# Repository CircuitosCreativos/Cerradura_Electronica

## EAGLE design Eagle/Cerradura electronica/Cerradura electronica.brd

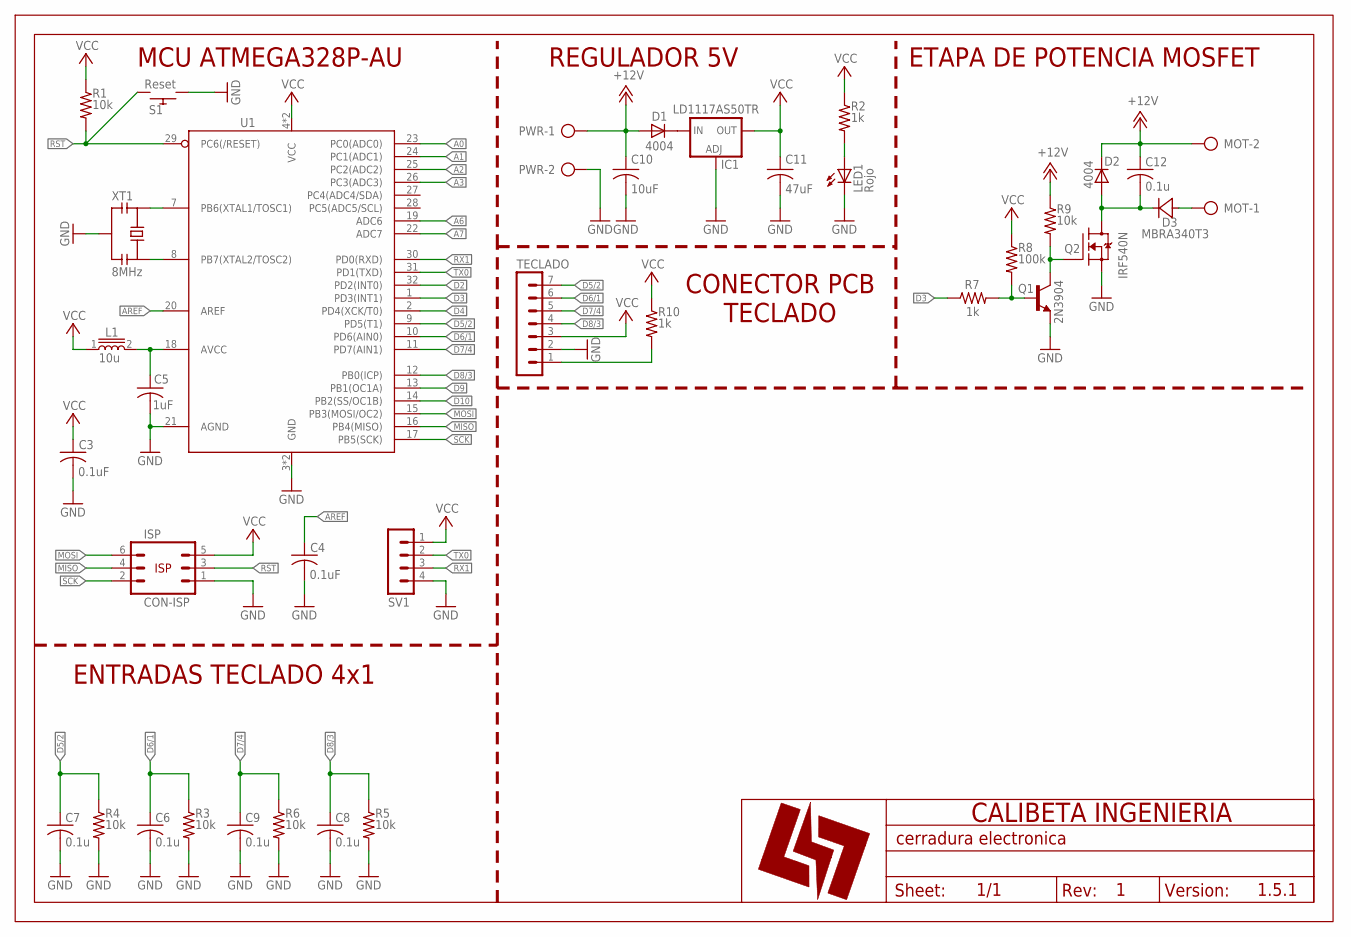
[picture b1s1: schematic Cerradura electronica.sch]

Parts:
C3, C4: 0.1uF; C0805
C5: 1uF; C0805
C6, C7, C8, C9, C12: 0.1u; C0805
C10: 10uF; C1206
C11: 47uF; C1206
D1, D2: 4004; DO-214AC
D3: MBRA340T3; SMA
IC1: LD1117AS50TR; SOT-223
ISP: CON-ISP; HEADER-M2X3
L1: 10u; L0805
LED1: Rojo; LED0805-ROJO
MOT: AK500-2
PWR: AK500-2
Q1: 2N3904; SOT-23_BEC
Q2: IRF540N; TO-263
R1, R3, R4, R5, R6, R9: 10k; R0805
R2, R7, R10: 1k; R0805
R8: 100k; R0805
S1: Reset; ST-SMD-6X3.5MM
SV1: MA04-1
TECLADO: MA07-1
U1: ATMEGA328P-AU; TQFP32
U$1: A4_H-LOGO; LOGO-10MM
XT1: 8MHz; 3-SMD

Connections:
+12V: C10.1, C12.1, D1.A, D2.K (C), MOT.2, PWR.1, R9.1
A0: U1.23 (PC0(ADC0))
A1: U1.24 (PC1(ADC1))
A2: U1.25 (PC2(ADC2))
A3: U1.26 (PC3(ADC3))
A6: U1.19 (ADC6)
A7: U1.22 (ADC7)
AREF: C4.1, U1.20 (AREF)
AVCC: C5.1, L1.2, U1.18 (AVCC)
D2: U1.32 (PD2(INT0))
D3: R7.1, U1.1 (PD3(INT1))
D4: U1.2 (PD4(XCK/T0))
D5/2: C7.1, R4.1, TECLADO.7, U1.9 (PD5(T1))
D6/1: C6.1, R3.1, TECLADO.6, U1.10 (PD6(AIN0))
D7/4: C9.1, R6.1, TECLADO.5, U1.11 (PD7(AIN1))
D8/3: C8.1, R5.1, TECLADO.4, U1.12 (PB0(ICP))
D9: U1.13 (PB1(OC1A))
D10: U1.14 (PB2(SS/OC1B))
GND: C3.2, C4.2, C5.2, C6.2, C7.2, C8.2, C9.2, C10.2, C11.2, IC1.1 (ADJ), ISP.1, LED1.C, PWR.2, Q1.E, Q2.3 (S), R3.2, R4.2, R5.2, R6.2, S1.1, SV1.4, TECLADO.2, U1.3 (GND), U1.5 (GND), U1.21 (AGND), XT1.2 (GND)
MISO: ISP.4, U1.16 (PB4(MISO))
MOSI: ISP.6, U1.15 (PB3(MOSI/OC2))
MOT: D3.A, MOT.1
unnamed: LED1.A, R2.2
unnamed: Q1.B, R7.2, R8.2
unnamed: D1.K (C), IC1.3 (IN)
unnamed: Q1.C, Q2.1 (G), R9.2
unnamed: U1.7 (PB6(XTAL1/TOSC1)), XT1.1 (X1)
unnamed: U1.8 (PB7(XTAL2/TOSC2)), XT1.3 (X2)
unnamed: R10.2, TECLADO.1
ON: C12.2, D2.A, D3.C, Q2.2 (D)
RST: ISP.3, R1.2, S1.2, U1.29 (PC6(/RESET))
RX1: SV1.3, U1.30 (PD0(RXD))
SCK: ISP.2, U1.17 (PB5(SCK))
TX0: SV1.2, U1.31 (PD1(TXD))
VCC: C3.1, C11.1, IC1.4 (OUT), ISP.5, L1.1, R1.1, R2.1, R8.1, R10.1, SV1.1, TECLADO.3, U1.4 (VCC), U1.6 (VCC)

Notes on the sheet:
MCU ATMEGA328P-AU
1.5.1
ENTRADAS TECLADO 4x1
REGULADOR 5V
ETAPA DE POTENCIA MOSFET
CONECTOR PCB TECLADO

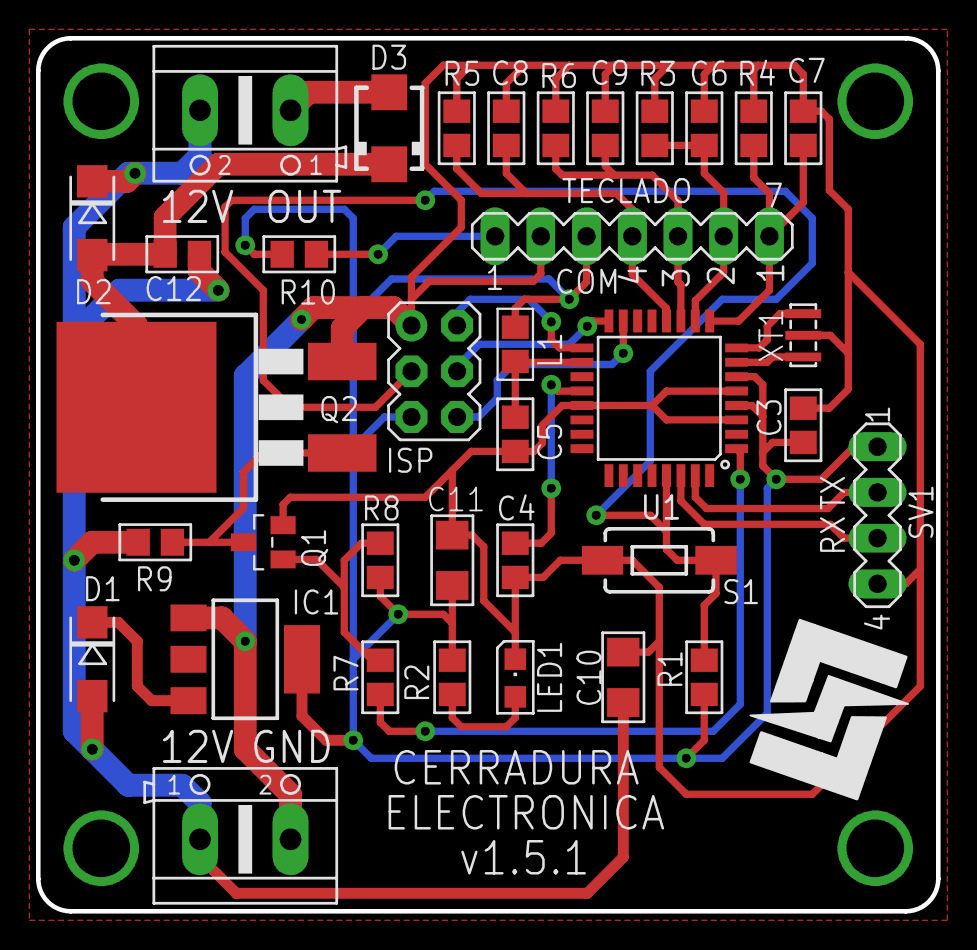
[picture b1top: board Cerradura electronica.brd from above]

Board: 2 copper layers, 50.0 x 48.5 mm, 37 parts (0 on the bottom side), 25 nets.

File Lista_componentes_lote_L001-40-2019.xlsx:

Cantidad | Valor | Device | Package | Parts | Description | Foto | Costo | 40
80 | 22pF | C-USC0805 | C0805 | C1, C2 | CAPACITOR, American symbol
40 | 10uF | C-USC0805 | C0805 | C10 | CAPACITOR, American symbol
40 | 47uF | C-USC1206 | C1206 | C11 | CAPACITOR, American symbol
280 | 0.1uF | C-USC0805 | C0805 | C3,C4,C6, C7, C8, C9, C12 | CAPACITOR, American symbol
40 | 1uF | C-USC0805 | C0805 | C5 | CAPACITOR, American symbol
100 | 4004 | DIODE-DO214AC | DO214AC | D1, D2 | RECTIFIER DIODE
40 | LD117AS50TR | LD117AS50TR | SOT223 | IC1 | Low drop fixed and adjustable positive voltage regulators 1 A
5 |  | MA20-2 | MA20-2 | ISP | REGLETA PIN HEADER DOBLE 40 PINES
100 | 10u | FERRITA-CHOKE | L0805 | L1 | Inductor para altas frecuencias 10uH
40 | Red | LEDCHIPLED_0805 | CHIPLED_0805 | LED1 | LED
40 | Green | LEDCHIPLED_0805 | CHIPLED_0805 | LED2 | LED
200 | PULSADOR5,2X5,2 | PULSADOR5,2X5,2 | SMT_5,2X5,2MM | P1,P2,P3,P4 | PULSADOR TACTIL SMD CON 5mm DE ALTURA
40 | 2N3904 | MMBT3904LT1-NPN-SOT23-BEC | SOT23-BEC | Q1 | NPN Transistror
40 | IRF540NS | IRF540NS | TO-252 | Q2 | MOSFET de cabal N 100V - 10A
1000 | 10k | R-US_R1206 | R1206 | R1, R3, R4, R5, R6, R8, R9 | RESISTOR, American symbol
1000 | 1k | R-US_R1206 | R1206 | R2, R7,R10 | RESISTOR, American symbol
40 | Reset | SWITCH-MOMENTARY-2-SMD-1101NE | TACTILE-SWITCH-1101NE | S1 | Various NO switches push buttons, reed, etc
20 |  | MA20-1 | MA20-1 | SV1 | REGLETA PIN HEADER SIMPLE 40 PINES
40 | ATMEGA328P_TQFP | ATMEGA328P_TQFP | TQFP32-08 | U1 | Microcontrolador Atmega328P-AU 32 pines
40 | 8MHz | CRYSTAL5032 | XT5032 | XT1 | CRYSTAL DE CUARZO SMD ENCAPSULADO 5032 |  |  | 0

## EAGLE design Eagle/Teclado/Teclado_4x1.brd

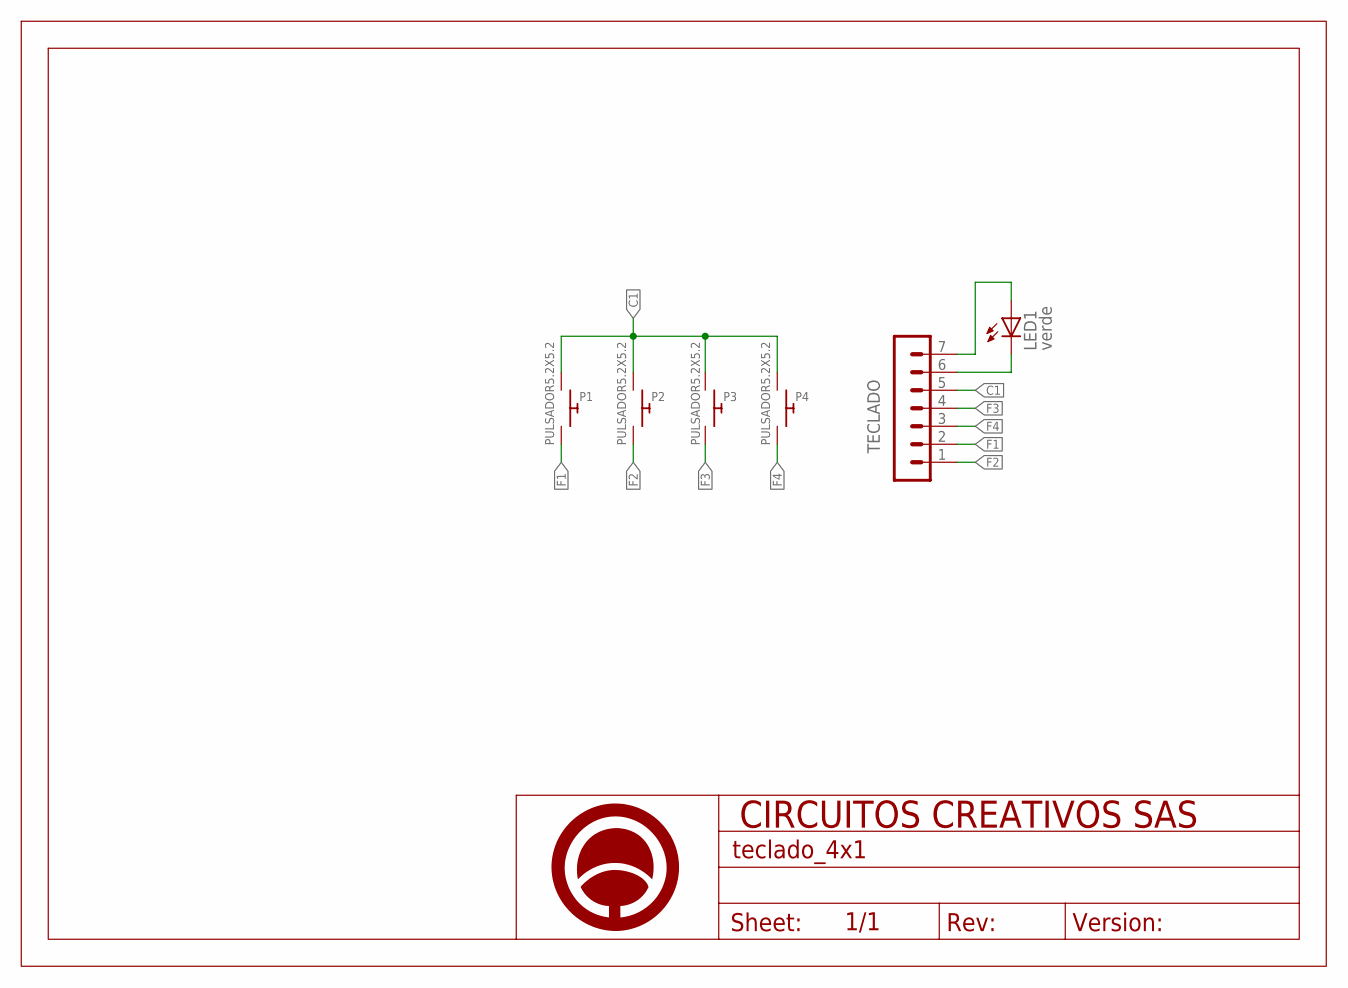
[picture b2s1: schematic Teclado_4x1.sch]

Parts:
LED1: verde; CHIP-LED0805
P1, P2, P3, P4: PULSADOR5.2X5.2; SMT_5.2X5.2MM
TECLADO: MA07-1
U$1: A5_HORIZONTAL; LOGO

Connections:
C1: P1.1, P1.2, P2.1, P2.2, P3.1, P3.2, P4.1, P4.2, TECLADO.5
F1: P1.3, P1.4, TECLADO.2
F2: P2.3, P2.4, TECLADO.1
F3: P3.3, P3.4, TECLADO.4
F4: P4.3, P4.4, TECLADO.3
unnamed: LED1.C, TECLADO.6
unnamed: LED1.A, TECLADO.7

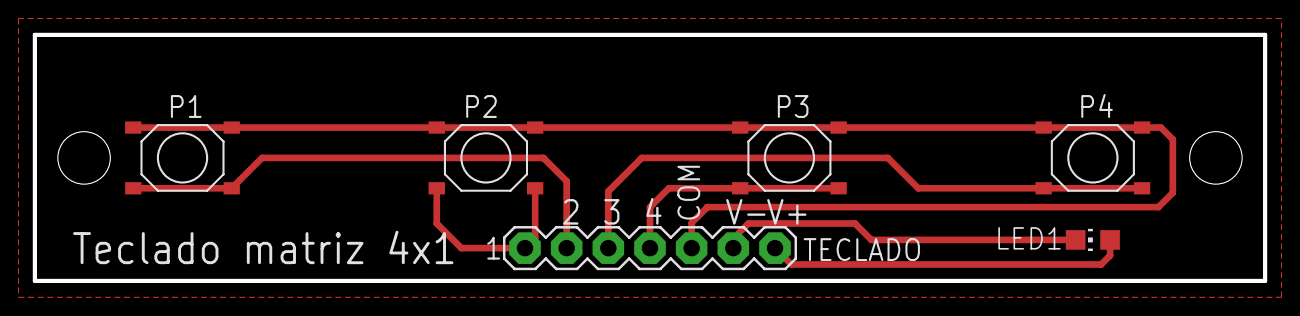
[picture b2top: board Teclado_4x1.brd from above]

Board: 2 copper layers, 75.0 x 15.0 mm, 7 parts (1 on the bottom side), 7 nets.

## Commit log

2019-01-16 Commit inicial, subido archivos v1.0
2019-01-27 Agrgado simulacion para verificar el nuevo Hardware
2019-01-28 Cambios en Firmware para el nuevo Hardware
2019-01-28 Completado SCH del nuevo Hardware al 50%
2019-01-31 Terminado regulador 5V y etapa de potencia
2019-02-01 Terminado el SCH, inicio del BRD
2019-02-01 Componentes ubicados, inicio ruteo
2019-02-01 Terminado ruteo, inicio revision 1.0
2019-02-06 Terminado PCB teclado
2019-03-02 Cambio solicitado por Segcontrol SAS
2019-06-07 Etapa de potencia con activacion GPS y teclado simultanea
2019-10-17 Inicio correciones en PCB
2019-10-17 correciones en PCB al 75%
2019-10-18 Terminado correciones
2019-10-18 Gerenado Gerber e imagenes
2021-06-19 Add BUZZER para mejorar la funcionalidad, terminado v1.5.1
